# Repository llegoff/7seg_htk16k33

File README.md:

[:fr:](LISEZMOI.md) [:uk:](README.md)

# 7seg_htk16k33

4*7 segments diplay + keyboard, drived by Holtek HT16K33

I2C interface

use Adafruit library (https://github.com/adafruit/Adafruit_LED_Backpack)

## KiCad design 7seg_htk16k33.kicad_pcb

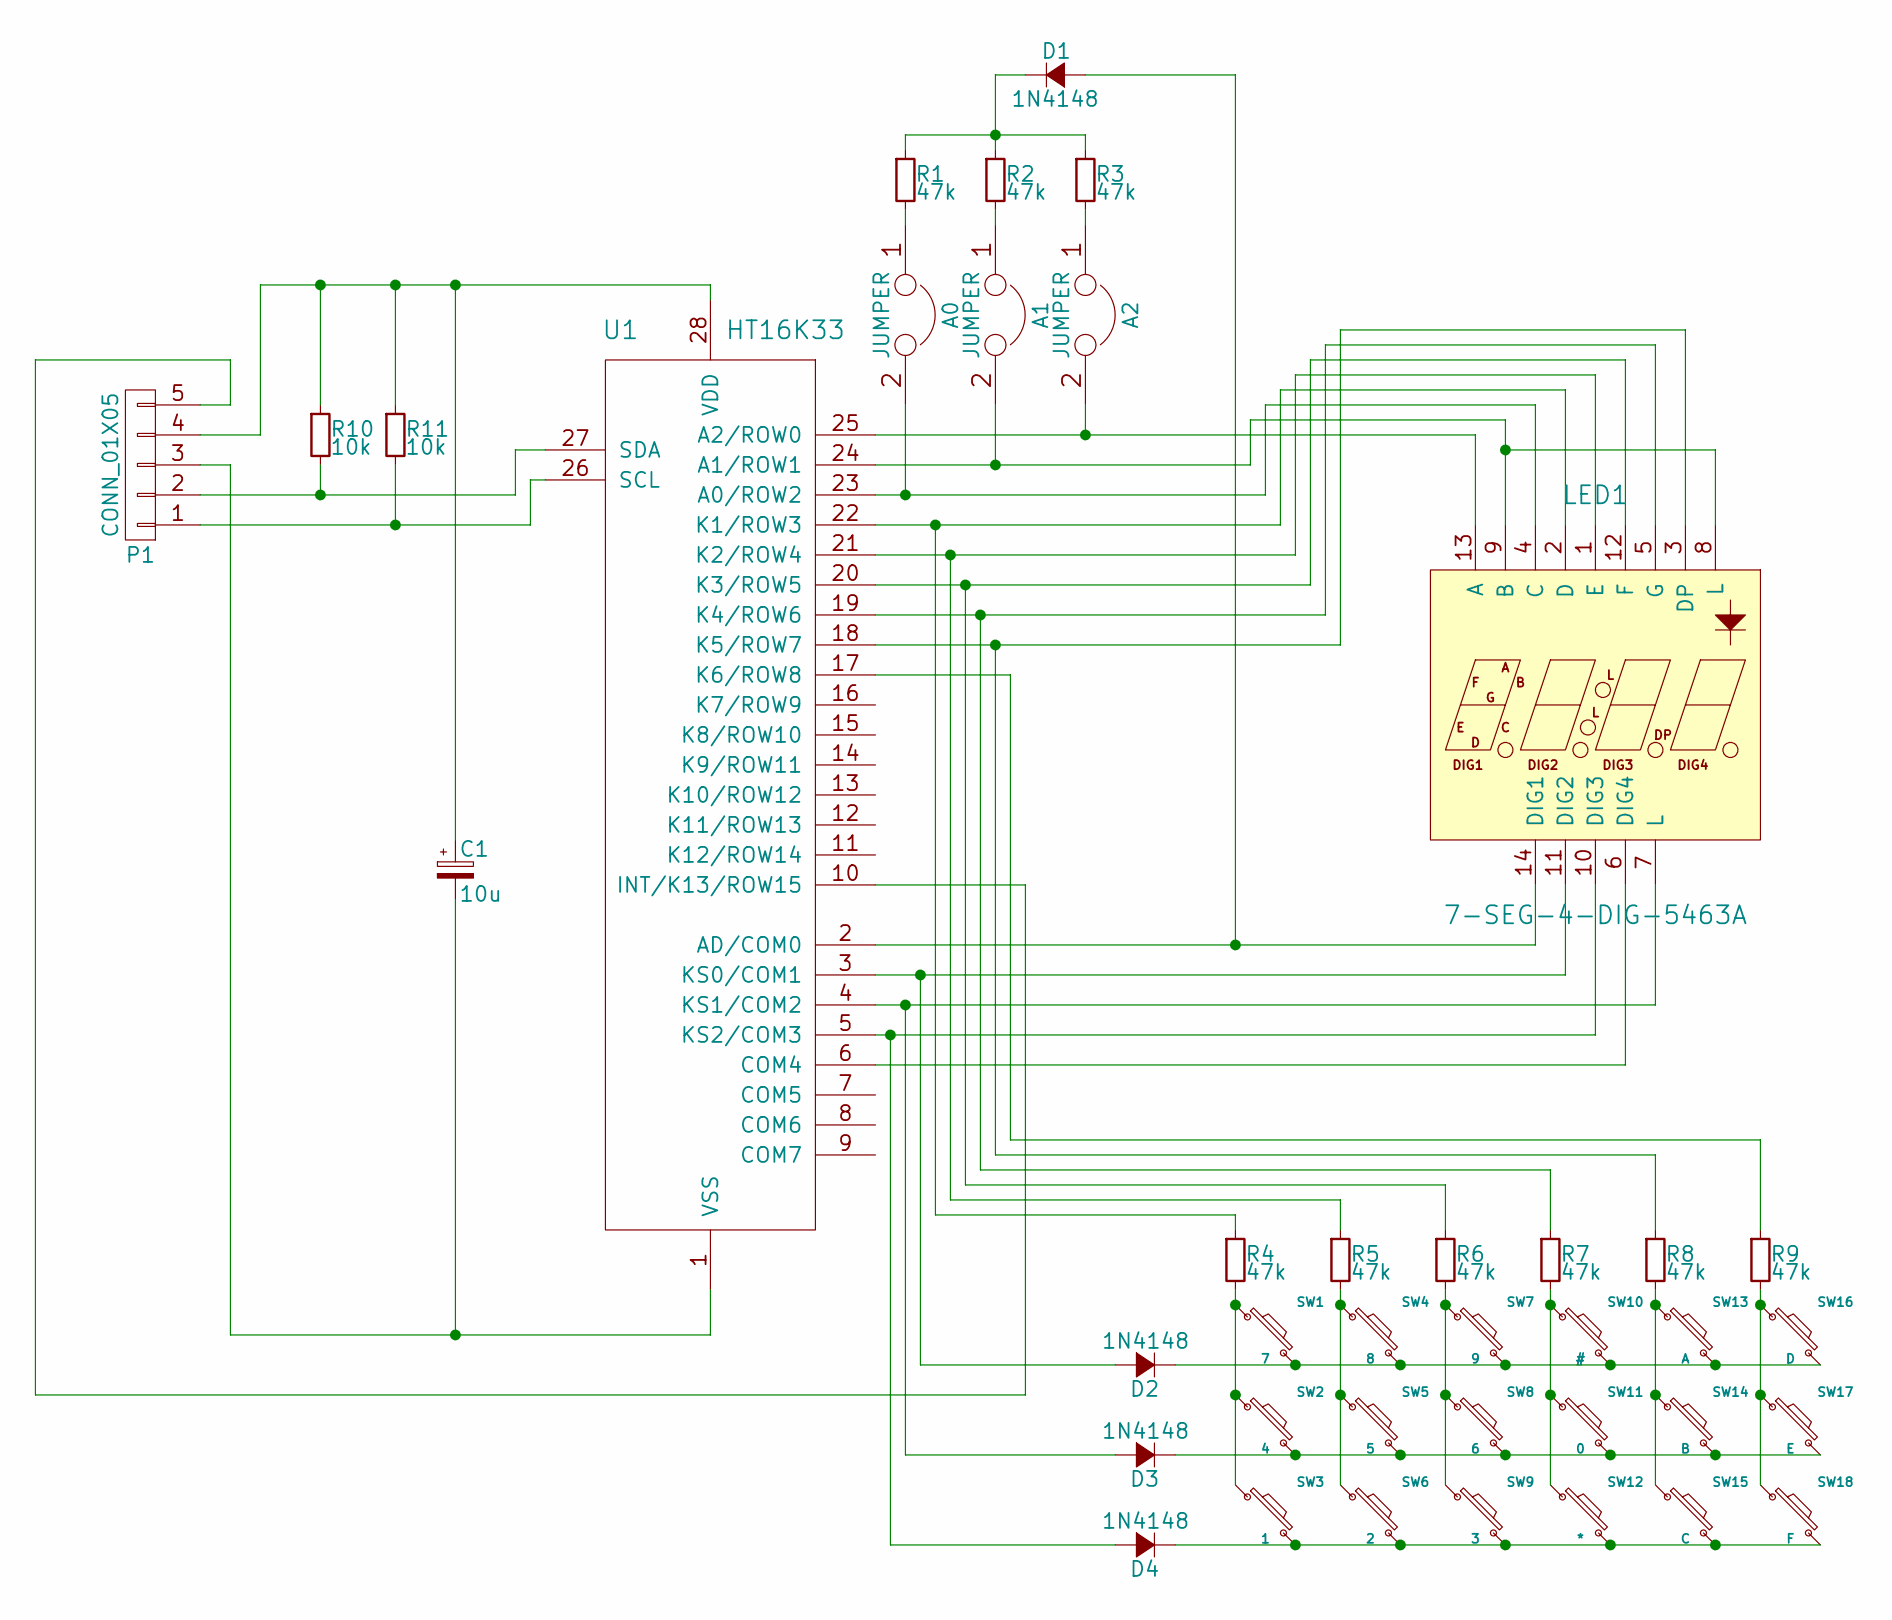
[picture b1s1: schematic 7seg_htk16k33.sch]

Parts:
A0, A1, A2: JUMPER; smd-JUMP-2
C1: 10u; TantalC_SizeB_EIA-3528_Reflow
D1, D2, D3, D4: 1N4148; Diode-Universal-MELF-RM10_Handsoldering
LED1: 7-SEG-4-DIG-5463A; 7-SEGMENT-4-DIGIT-5463
P1: CONN_01X05; Pin_Header_Straight_1x05
R1, R2, R3, R4, R5, R6, R7, R8, R9: 47k; R_0805
R10, R11: 10k; R_0805
SW1: 7; SW_PUSH_SMALL
SW2: 4; SW_PUSH_SMALL
SW3: 1; SW_PUSH_SMALL
SW4: 8; SW_PUSH_SMALL
SW5: 5; SW_PUSH_SMALL
SW6: 2; SW_PUSH_SMALL
SW7: 9; SW_PUSH_SMALL
SW8: 6; SW_PUSH_SMALL
SW9: 3; SW_PUSH_SMALL
SW10: #; SW_PUSH_SMALL
SW11: 0; SW_PUSH_SMALL
SW12: *; SW_PUSH_SMALL
SW13: A; SW_PUSH_SMALL
SW14: B; SW_PUSH_SMALL
SW15: C; SW_PUSH_SMALL
SW16: D; SW_PUSH_SMALL
SW17: E; SW_PUSH_SMALL
SW18: F; SW_PUSH_SMALL
U1: HT16K33; SOIC-28_7.5x17.9mm_Pitch1.27mm

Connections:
unnamed: A0.1, R1.2
unnamed: A0.2, LED1.4 (C), U1.23 (A0/ROW2)
unnamed: A1.1, R2.2
unnamed: A1.2, LED1.8 (L), LED1.9 (B), U1.24 (A1/ROW1)
unnamed: A2.1, R3.2
unnamed: A2.2, LED1.13 (A), U1.25 (A2/ROW0)
unnamed: C1.1, P1.4, R10.1, R11.1, U1.28 (VDD)
unnamed: C1.2, P1.3, U1.1 (VSS)
unnamed: D1.1 (K), R1.1, R2.1, R3.1
unnamed: D1.2 (A), LED1.14 (DIG1), U1.2 (AD/COM0)
unnamed: D2.1 (K), SW1.2, SW4.2, SW7.2, SW10.2, SW13.2, SW16.2
unnamed: D2.2 (A), LED1.11 (DIG2), U1.3 (KS0/COM1)
unnamed: D3.1 (K), SW2.2, SW5.2, SW8.2, SW11.2, SW14.2, SW17.2
unnamed: D3.2 (A), LED1.7 (L), U1.4 (KS1/COM2)
unnamed: D4.1 (K), SW3.2, SW6.2, SW9.2, SW12.2, SW15.2, SW18.2
unnamed: D4.2 (A), LED1.10 (DIG3), U1.5 (KS2/COM3)
unnamed: LED1.1 (E), R5.1, U1.21 (K2/ROW4)
unnamed: LED1.2 (D), R4.1, U1.22 (K1/ROW3)
unnamed: LED1.3 (DP), R8.1, U1.18 (K5/ROW7)
unnamed: LED1.5 (G), R7.1, U1.19 (K4/ROW6)
unnamed: LED1.6 (DIG4), U1.6 (COM4)
unnamed: LED1.12 (F), R6.1, U1.20 (K3/ROW5)
unnamed: P1.1, R11.2, U1.26 (SCL)
unnamed: P1.2, R10.2, U1.27 (SDA)
unnamed: P1.5, U1.10 (INT/K13/ROW15)
unnamed: R4.2, SW1.1, SW2.1, SW3.1
unnamed: R5.2, SW4.1, SW5.1, SW6.1
unnamed: R6.2, SW7.1, SW8.1, SW9.1
unnamed: R7.2, SW10.1, SW11.1, SW12.1
unnamed: R8.2, SW13.1, SW14.1, SW15.1
unnamed: R9.1, U1.17 (K6/ROW8)
unnamed: R9.2, SW16.1, SW17.1, SW18.1

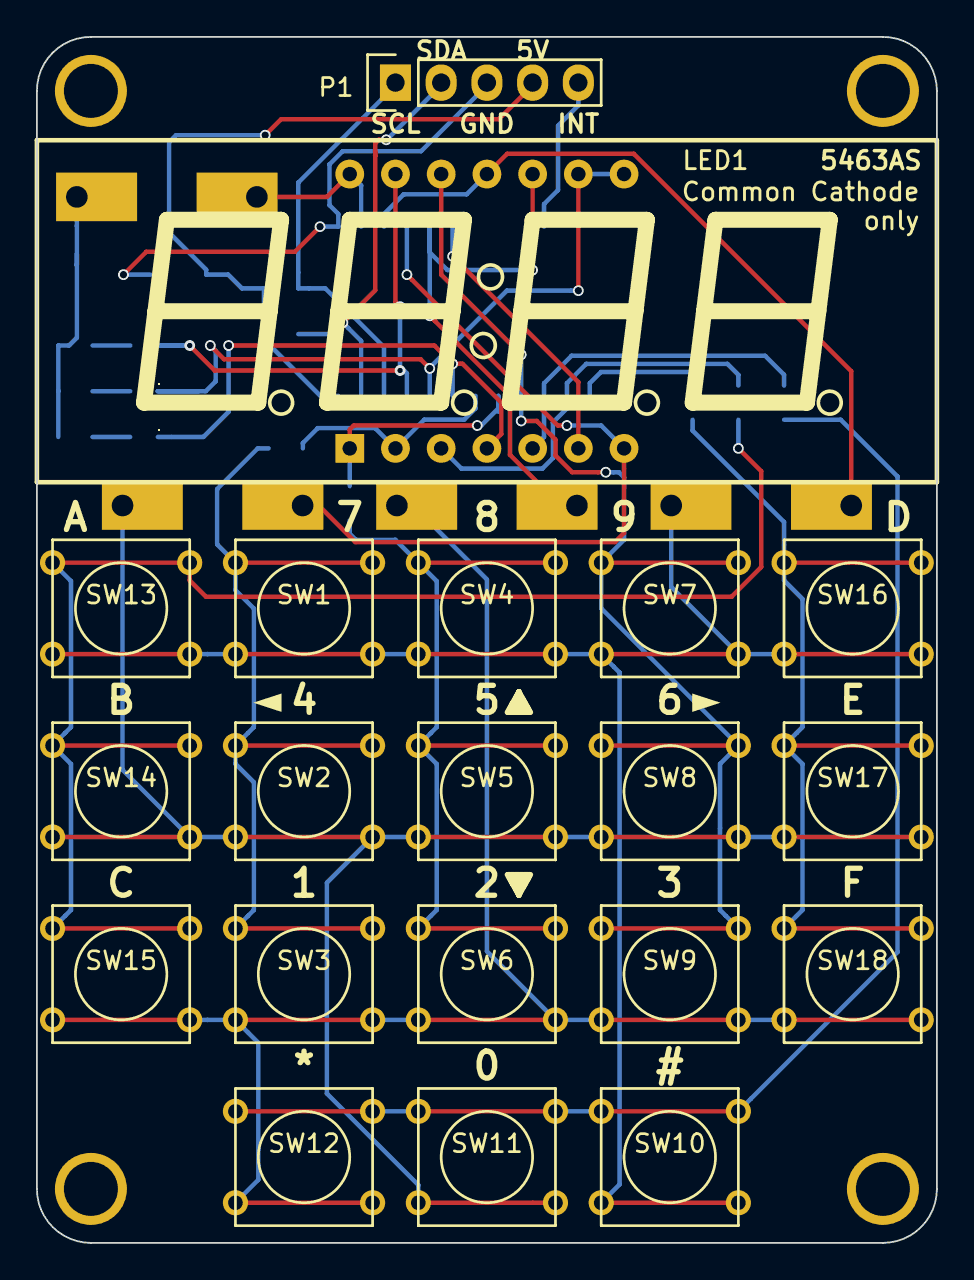
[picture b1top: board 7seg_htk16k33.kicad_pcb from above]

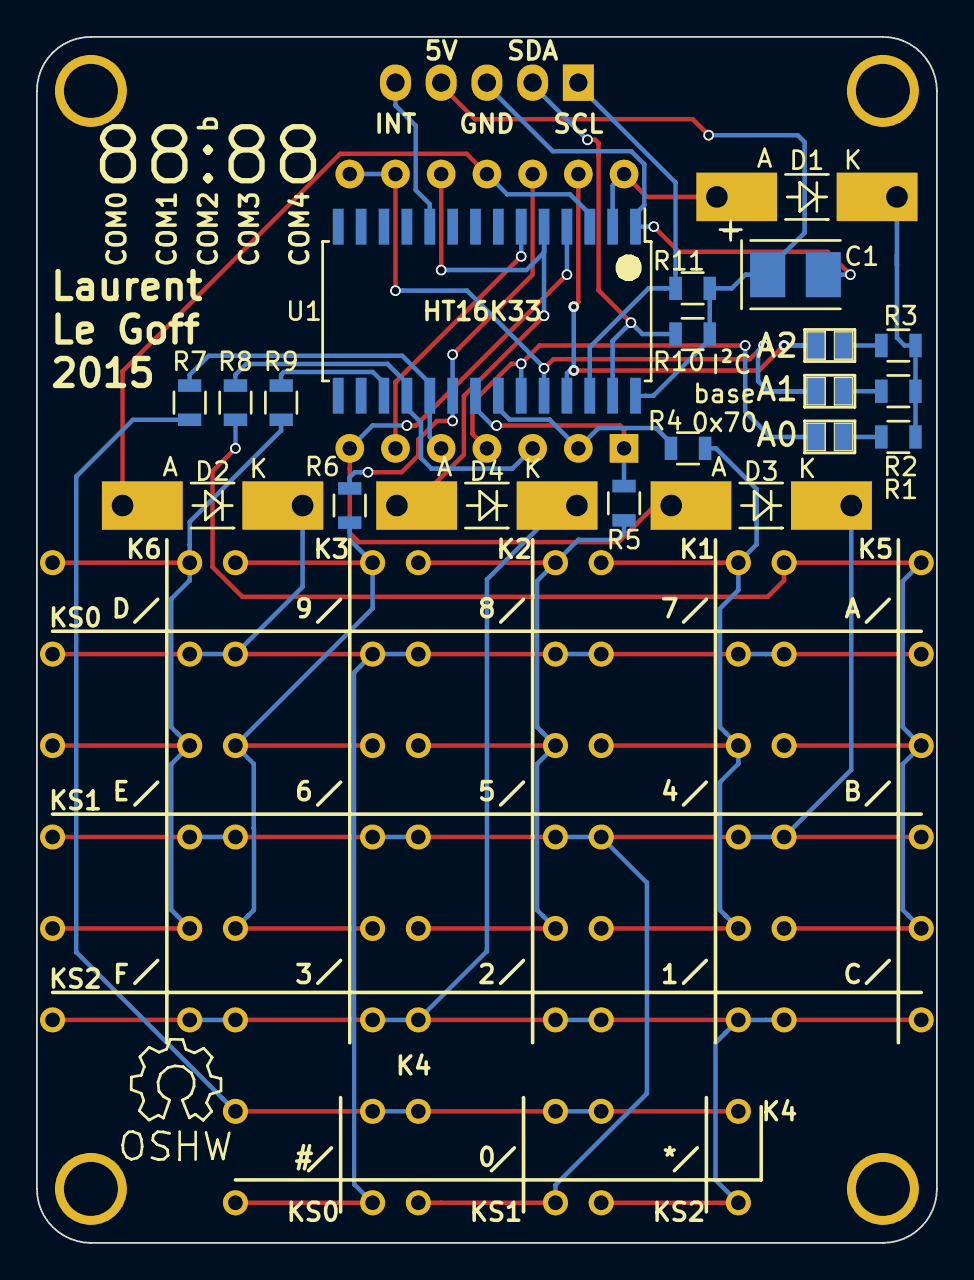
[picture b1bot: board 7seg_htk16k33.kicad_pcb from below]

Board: 2 copper layers, 50.0 x 67.0 mm, 40 parts (20 on the bottom side), 32 nets.

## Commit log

2017-10-24 Create test
